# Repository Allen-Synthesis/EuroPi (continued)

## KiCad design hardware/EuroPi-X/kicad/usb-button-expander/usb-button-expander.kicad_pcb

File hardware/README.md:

# Hardware Overview
There are multiple versions of the hardware documented in this directory, the original EuroPi (through-hole), the new EuroPi-SMD (surface-mount), and a stripboard version (stripboard). Each has a different build guide and bill of materials, so make sure you follow the one you want to build.

**[surface-mount](surface-mount/)**: The simplest to DIY as you only need to solder on the components which stick through the panel, i.e. the jacks, knobs etc. All of the other circuitry is soldered onto the PCB already.

**[through-hole](through-hole/)**: A slightly more in depth build as you need to solder on every component, however only through-hole components are used, so this isn't as hard as it sounds. This is the build most people have made and was previously the only publicly available build at all.

**[stripboard](stripboard/)**: A much rougher layout and does not use a PCB at all, but instead uses 'stripboard'. This hasn't been tested nearly as much as the other two, but people have successfully built it and shared their version on Discord. Not developed or maintained by Allen Synthesis.

# Hardware Specifications
All hardware variants share the same specifications as the components and schematics are the same.

## Outputs
- 1k Output Impedance
- RC filter smoothed PWM
- ~1.5kHz Maximum usable frequency (without changing RC values)
- 0-10V

## Analogue Input
- 100k Input Impedance
- 0-12V Readable Range
- Protected for ±12V (TL074 limits, MCP6002 will always clip to ±3.3V)

## Digital Input
- 100k Input Impedance
- 0.8V threshold to read as high

## OLED
- SSD1306 0.91"
- 128 x 32 pixels
- I2C Protocol

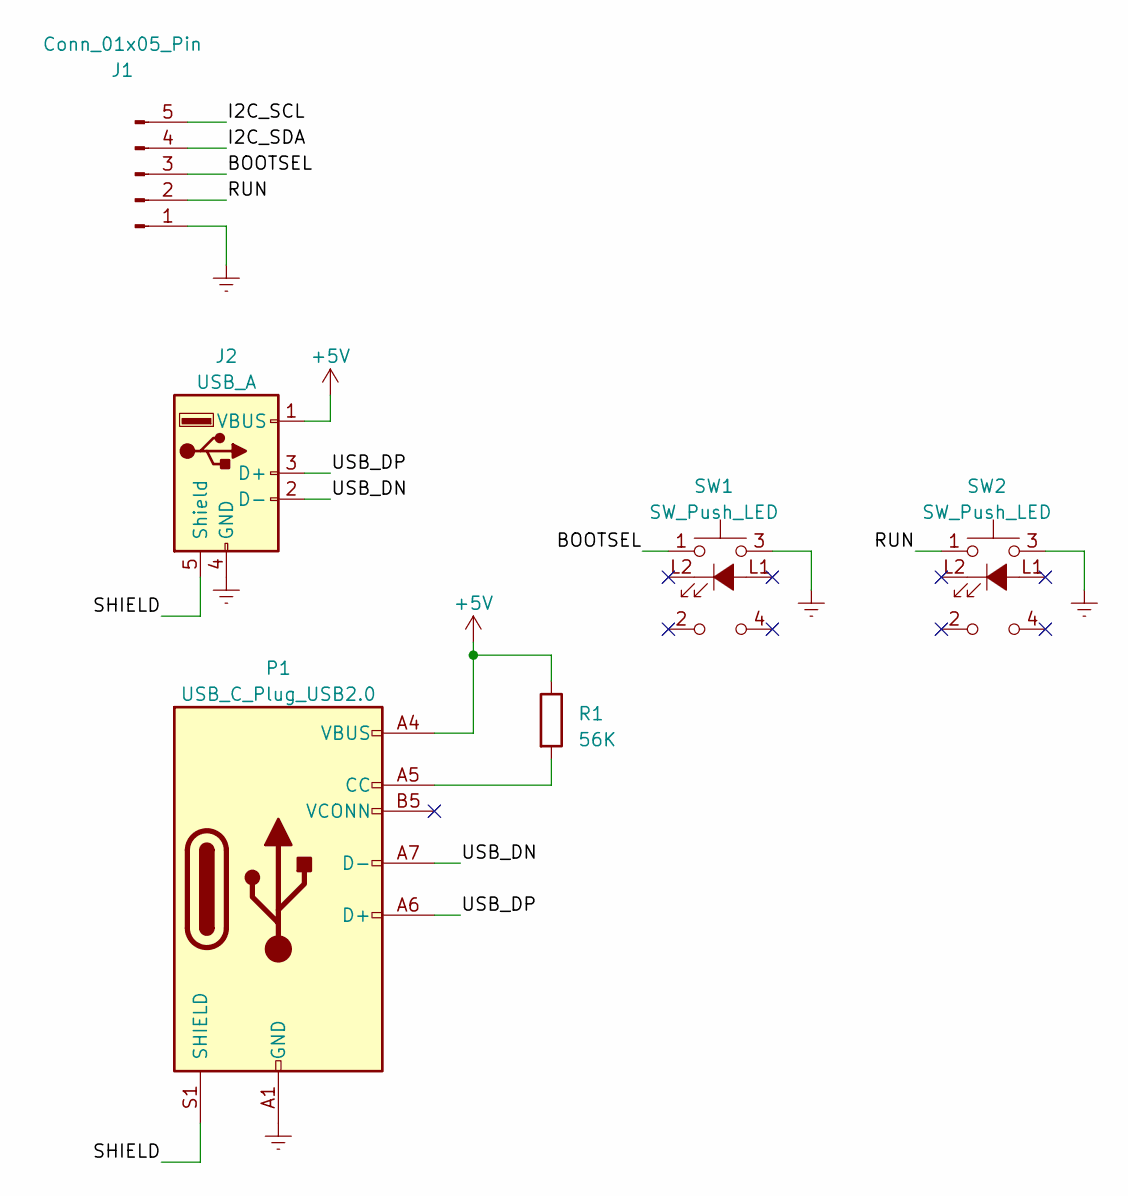
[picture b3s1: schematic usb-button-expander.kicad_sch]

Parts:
J1: Conn_01x05_Pin; PinHeader_1x05_P2.54mm_Vertical
J2: USB_A; CN22155 USB 2.0 Female Connector
P1: USB_C_Plug_USB2.0; USB_C_Receptacle_GCT_USB4115-03-C
R1: 56K; R_0402_1005Metric
SW1, SW2: SW_Push_LED; PB01-109TL low Profile Illuminated Button

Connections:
+5V: J2.1 (VBUS), P1.A4 (VBUS), P1.A9 (VBUS), P1.B4 (VBUS), P1.B9 (VBUS), R1.1
/BOOTSEL: J1.3, SW1.1
/I2C_SCL: J1.5
/I2C_SDA: J1.4
/RUN: J1.2, SW2.1
/SHIELD: J2.5 (Shield), P1.S1 (SHIELD)
/USB_DN: J2.2 (D-), P1.A7 (D-)
/USB_DP: J2.3 (D+), P1.A6 (D+)
Earth: J1.1, J2.4 (GND), P1.A1 (GND), P1.A12 (GND), P1.B1 (GND), P1.B12 (GND), SW1.3, SW2.3
unnamed: P1.A5 (CC), R1.2

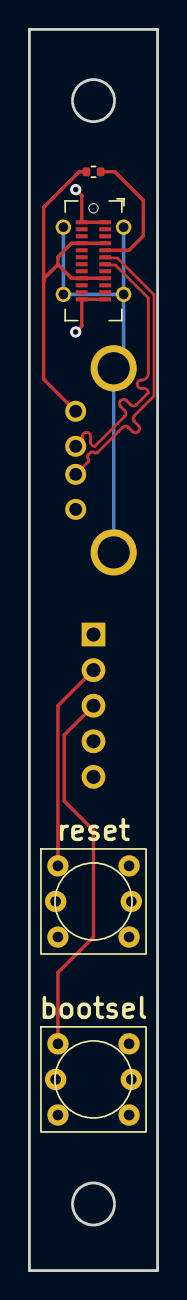
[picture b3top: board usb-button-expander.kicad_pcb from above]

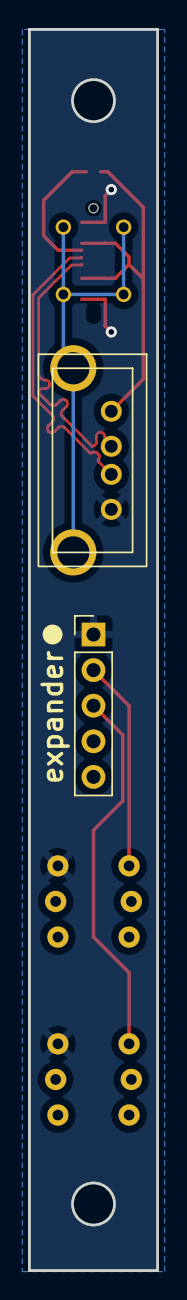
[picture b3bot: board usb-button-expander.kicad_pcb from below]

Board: 2 copper layers, 9.1 x 88.6 mm, 6 parts (2 on the bottom side), 8 nets.

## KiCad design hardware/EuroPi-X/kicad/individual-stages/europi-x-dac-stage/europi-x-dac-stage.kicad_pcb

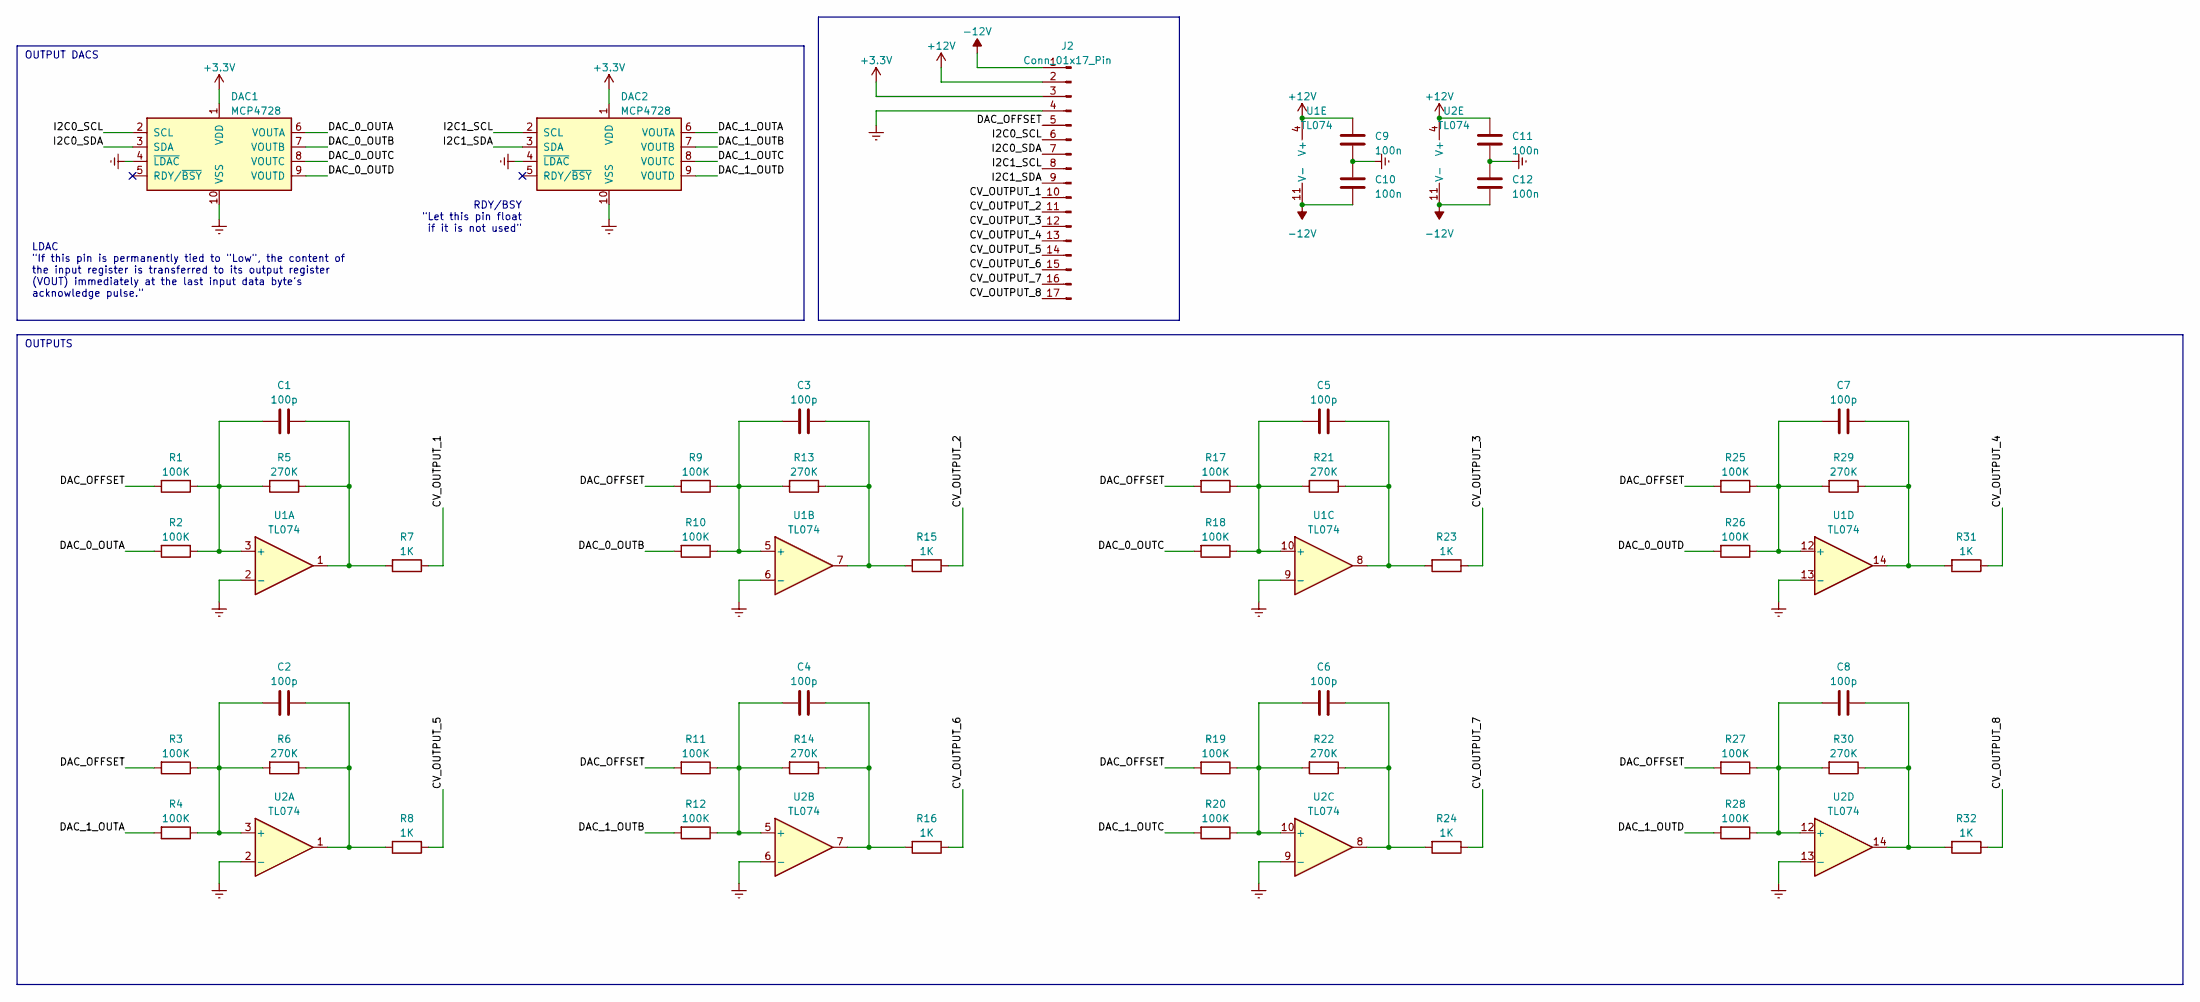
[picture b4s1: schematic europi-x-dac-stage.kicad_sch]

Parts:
C1, C2, C3, C4, C5, C6, C7, C8: 100p; C_0402_1005Metric
C9, C10, C11, C12: 100n; C_0402_1005Metric
DAC1, DAC2: MCP4728; MSOP-10_3x3mm_P0.5mm
J2: Conn_01x17_Pin; PinHeader_1x17_P2.54mm_Vertical
R1, R2, R3, R4, R9, R10, R11, R12, R17, R18, R19, R20, R25, R26, R27, R28: 100K; R_0402_1005Metric
R5, R6, R13, R14, R21, R22, R29, R30: 270K; R_0402_1005Metric
R7, R8, R15, R16, R23, R24, R31, R32: 1K; R_0402_1005Metric
U1, U2: TL074; SOIC-14_3.9x8.7mm_P1.27mm

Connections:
+3.3V: DAC1.1 (VDD), DAC2.1 (VDD), J2.3
+12V: C9.1, C11.1, J2.2, U1.4 (V+), U2.4 (V+)
-12V: C10.2, C12.2, J2.1, U1.11 (V-), U2.11 (V-)
/CV_OUTPUT_1: J2.10, R7.1
/CV_OUTPUT_2: J2.11, R15.1
/CV_OUTPUT_3: J2.12, R23.1
/CV_OUTPUT_4: J2.13, R31.1
/CV_OUTPUT_5: J2.14, R8.1
/CV_OUTPUT_6: J2.15, R16.1
/CV_OUTPUT_7: J2.16, R24.1
/CV_OUTPUT_8: J2.17, R32.1
/DAC_0_OUTA: DAC1.6 (VOUTA), R2.2
/DAC_0_OUTB: DAC1.7 (VOUTB), R10.2
/DAC_0_OUTC: DAC1.8 (VOUTC), R18.2
/DAC_0_OUTD: DAC1.9 (VOUTD), R26.2
/DAC_1_OUTA: DAC2.6 (VOUTA), R4.2
/DAC_1_OUTB: DAC2.7 (VOUTB), R12.2
/DAC_1_OUTC: DAC2.8 (VOUTC), R20.2
/DAC_1_OUTD: DAC2.9 (VOUTD), R28.2
/DAC_OFFSET: J2.5, R1.2, R3.2, R9.2, R11.2, R17.2, R19.2, R25.2, R27.2
/I2C0_SCL: DAC1.2 (SCL), J2.6
/I2C0_SDA: DAC1.3 (SDA), J2.7
/I2C1_SCL: DAC2.2 (SCL), J2.8
/I2C1_SDA: DAC2.3 (SDA), J2.9
Earth: C9.2, C10.1, C11.2, C12.1, DAC1.4 (~LDAC), DAC1.10 (VSS), DAC2.4 (~LDAC), DAC2.10 (VSS), J2.4, U1.2 (-), U1.6 (-), U1.9 (-), U1.13 (-), U2.2 (-), U2.6 (-), U2.9 (-), U2.13 (-)
unnamed: C1.2, R5.1, R7.2, U1.1
unnamed: C2.2, R6.1, R8.2, U2.1
unnamed: C3.2, R13.1, R15.2, U1.7
unnamed: C4.2, R14.1, R16.2, U2.7
unnamed: C5.2, R21.1, R23.2, U1.8
unnamed: C6.2, R22.1, R24.2, U2.8
unnamed: C7.2, R29.1, R31.2, U1.14
unnamed: C8.2, R30.1, R32.2, U2.14
unnamed: C1.1, R1.1, R2.1, R5.2, U1.3 (+)
unnamed: C3.1, R9.1, R10.1, R13.2, U1.5 (+)
unnamed: C5.1, R17.1, R18.1, R21.2, U1.10 (+)
unnamed: C7.1, R25.1, R26.1, R29.2, U1.12 (+)
unnamed: C2.1, R3.1, R4.1, R6.2, U2.3 (+)
unnamed: C4.1, R11.1, R12.1, R14.2, U2.5 (+)
unnamed: C6.1, R19.1, R20.1, R22.2, U2.10 (+)
unnamed: C8.1, R27.1, R28.1, R30.2, U2.12 (+)

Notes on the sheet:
LDAC "If this pin is permanently tied to "Low", the content of the input register is transferred to its output register (VOUT) immediately at the last input data byte's acknowledge pulse."
RDY/BSY "Let this pin float if it is not used"
OUTPUTS
OUTPUT DACS

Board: 2 copper layers, 49 parts (0 on the bottom side), 41 nets, no tracks yet.

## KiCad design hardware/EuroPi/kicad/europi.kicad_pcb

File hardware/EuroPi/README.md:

# Hardware Specifications

## Outputs
- 1k Output Impedance
- RC filter smoothed PWM
- ~1.5kHz Maximum usable frequency (without changing RC values)
- 0.000176V Maximum ripple peak-to-peak
- 0.0108s Settle time from 0% to 90% duty cycle
- 0-10V

## Analogue Input
- 100k Input Impedance
- 0-12V Readable Range
- Protected for ±36V (TL074 limits, MCP6002 will always clip to ±3.3V)

## Digital Input
- 100k Input Impedance
- 0.8V threshold to read as high

## OLED
- SSD1306 0.91"
- 128 x 32 pixels
- I2C Protocol

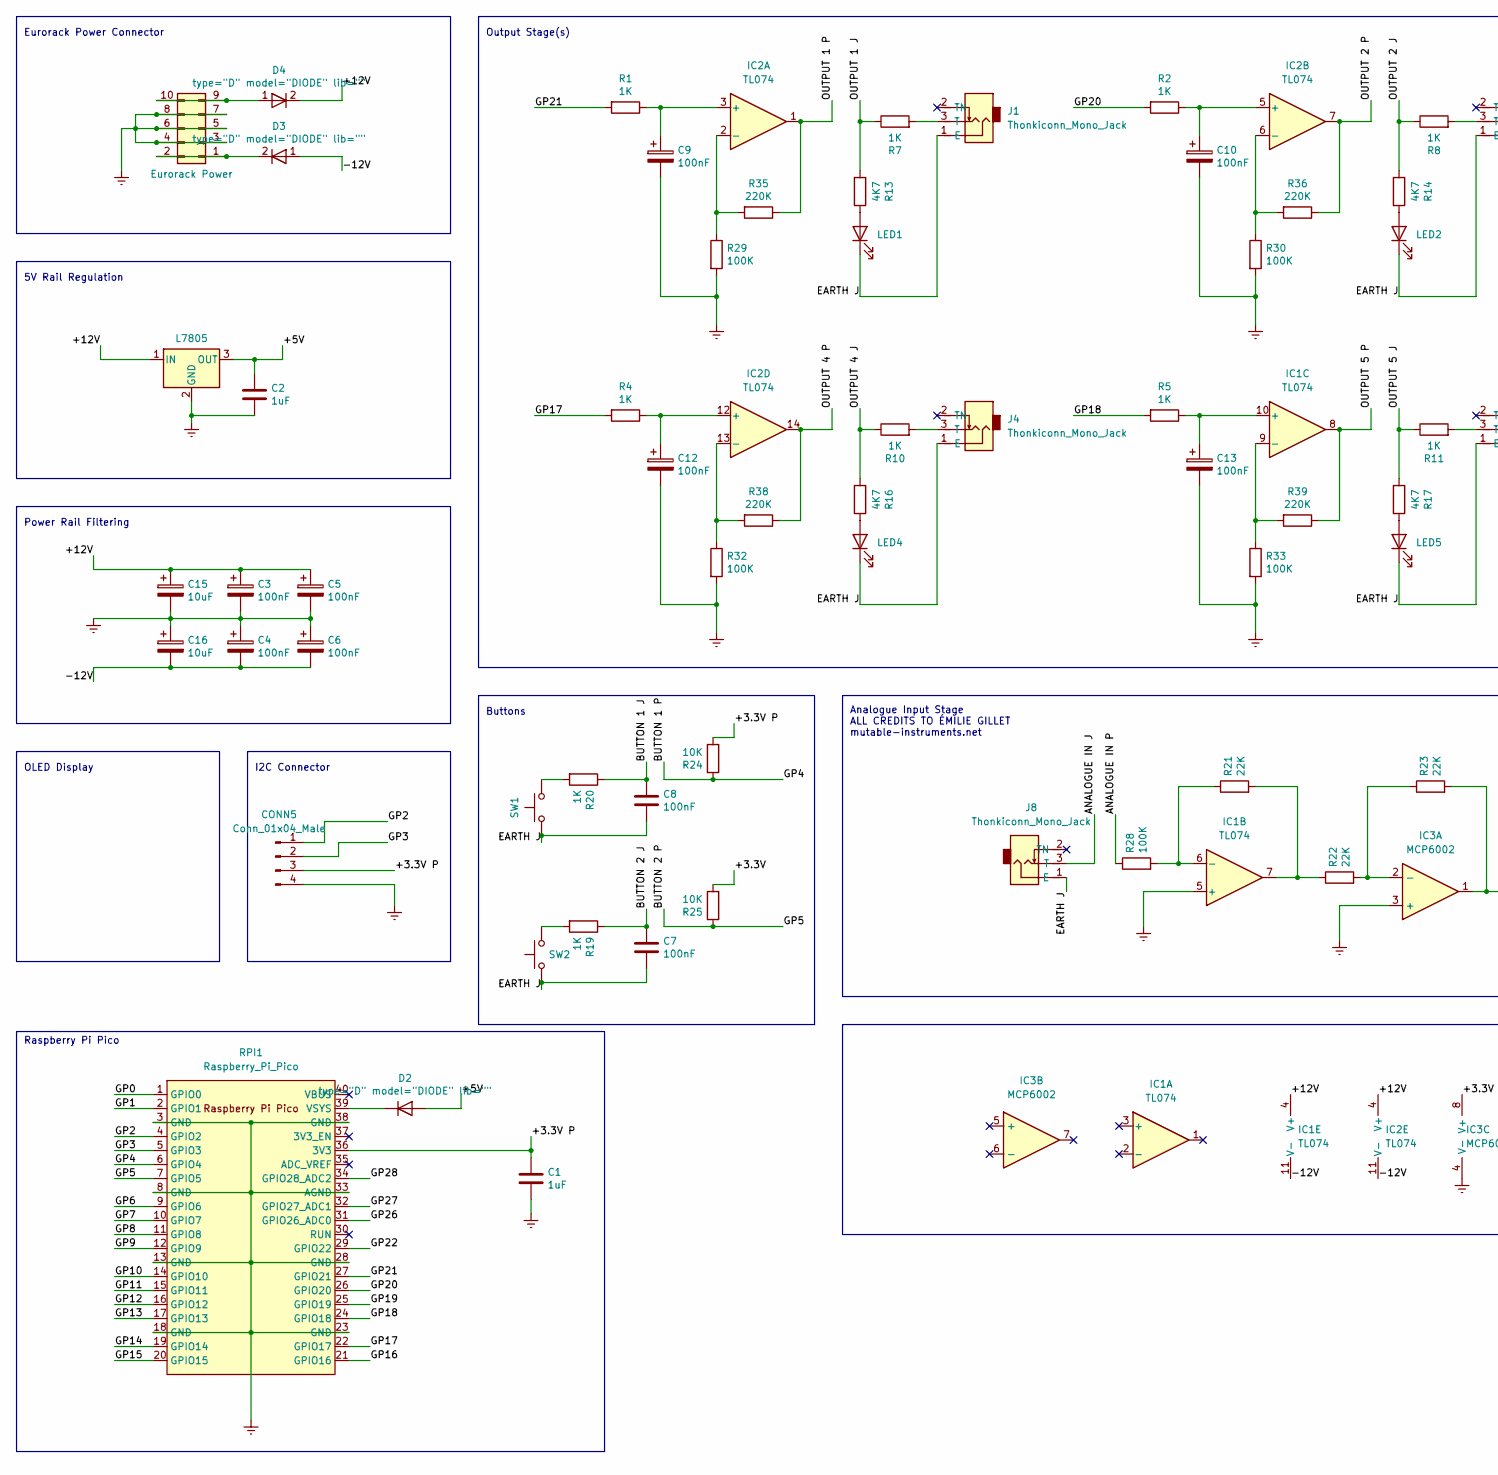
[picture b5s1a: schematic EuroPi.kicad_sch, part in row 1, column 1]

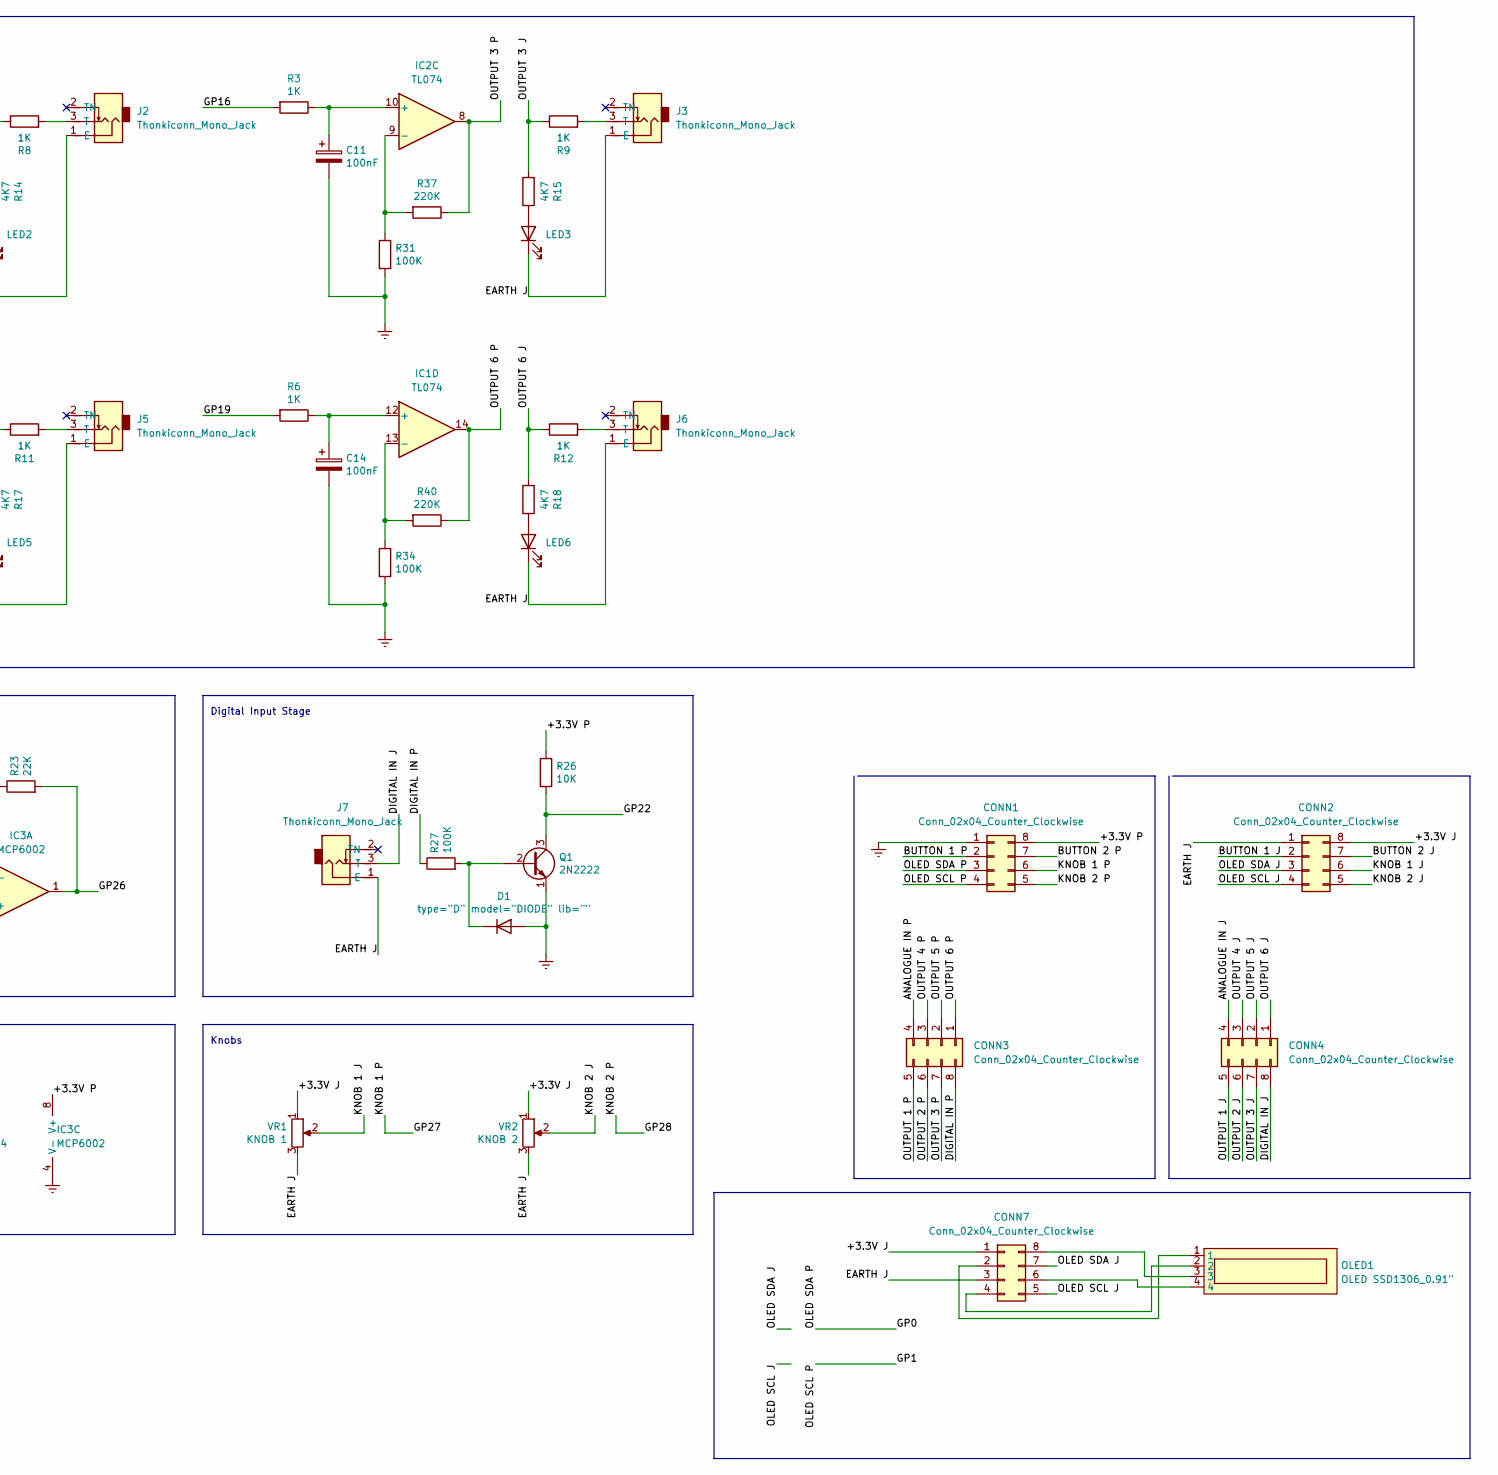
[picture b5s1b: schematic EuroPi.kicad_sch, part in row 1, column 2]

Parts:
C1, C2: 1uF; CP_Radial_D5.0mm_P2.50mm
C3, C4, C5, C6, C7, C8, C9, C10, C11, C12, C13, C14: 100nF; Capacitor Small Non-Polarised
C15, C16: 10uF; CP_Radial_D8.0mm_P3.80mm
CONN1, CONN2, CONN3, CONN4, CONN7: Conn_02x04_Counter_Clockwise; PinHeader_2x04_P2.54mm_Vertical
CONN5: Conn_01x04_Male; PinHeader_1x04_P2.54mm_Vertical
D1, D2, D3, D4: type="D" model="DIODE" lib=""; Schottky Diode
EuroPower1: Eurorack Power; Eurorack Power Header Unlabeled
IC1, IC2: TL074; DIP-14 IC Socket
IC3: MCP6002; DIP-8 IC Socket
J1, J2, J3, J4, J5, J6, J7, J8: Thonkiconn_Mono_Jack; Thonkiconn Mono Jack
LED1, LED2, LED3, LED4, LED5, LED6: LED; LED 3mm
OLED1: OLED SSD1306_0.91"; OLED SSD1306 0.91
Q1: 2N2222; TO-92
R1, R2, R3, R4, R5, R6, R7, R8, R9, R10, R11, R12, R19, R20: 1K; Resistor 0.25W Through-Hole
R13, R14, R15, R16, R17, R18: 4K7; Resistor 0.25W Through-Hole
R21, R22, R23: 22K; Resistor 0.25W Through-Hole
R24, R25, R26: 10K; Resistor 0.25W Through-Hole
R27, R28, R29, R30, R31, R32, R33, R34: 100K; Resistor 0.25W Through-Hole
R35, R36, R37, R38, R39, R40: 220K; Resistor 0.25W Through-Hole
REG1: L7805; TO-220-3_Vertical
RPI1: Raspberry_Pi_Pico; Raspberry Pi Pico
SW1, SW2: SW_Push; Switch Tactile Momentary C&K
VR1: KNOB 1; Potentiometer 9mm Vertical Linear Centred
VR2: KNOB 2; Potentiometer 9mm Vertical Linear Centred

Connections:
/+3.3V: R25.2
/+3.3V J: CONN2.8, CONN7.1, VR1.1, VR2.1
/+3.3V P: C1.1, CONN1.8, CONN5.3, IC3.8 (V+), R24.2, R26.1, RPI1.36 (3V3)
/+5V: C2.1, D2.1 (A), REG1.3 (OUT)
/+12V: C3.1, C5.1, C15.1, D4.2 (K), IC1.4 (V+), IC2.4 (V+), REG1.1 (IN)
/-12V: C4.2, C6.2, C16.2, D3.1 (A), IC1.11 (V-), IC2.11 (V-)
/ANALOGUE IN J: CONN4.4, J8.3 (T)
/ANALOGUE IN P: CONN3.4, R28.1
/BUTTON 1 J: C8.1, CONN2.2, R20.1
/BUTTON 1 P: CONN1.2, R24.1, RPI1.6 (GPIO4)
/BUTTON 2 J: C7.1, CONN2.7, R19.1
/BUTTON 2 P: CONN1.7, R25.1, RPI1.7 (GPIO5)
/DIGITAL IN J: CONN4.8, J7.3 (T)
/DIGITAL IN P: CONN3.8, R27.1
/EARTH J: C7.2, C8.2, CONN2.1, CONN7.3, J1.1 (E), J2.1 (E), J3.1 (E), J4.1 (E), J5.1 (E), J6.1 (E), J7.1 (E), J8.1 (E), LED1.1 (K), LED2.1 (K), LED3.1 (K), LED4.1 (K), LED5.1 (K), LED6.1 (K), SW1.1, SW2.1, VR1.3, VR2.3
/GP0: CONN1.3, RPI1.1 (GPIO0)
/GP1: CONN1.4, RPI1.2 (GPIO1)
/GP2: CONN5.1, RPI1.4 (GPIO2)
/GP3: CONN5.2, RPI1.5 (GPIO3)
/GP6: RPI1.9 (GPIO6)
/GP7: RPI1.10 (GPIO7)
/GP8: RPI1.11 (GPIO8)
/GP9: RPI1.12 (GPIO9)
/GP10: RPI1.14 (GPIO10)
/GP11: RPI1.15 (GPIO11)
/GP12: RPI1.16 (GPIO12)
/GP13: RPI1.17 (GPIO13)
/GP14: RPI1.19 (GPIO14)
/GP15: RPI1.20 (GPIO15)
/GP16: R3.2, RPI1.21 (GPIO16)
/GP17: R4.2, RPI1.22 (GPIO17)
/GP18: R5.2, RPI1.24 (GPIO18)
/GP19: R6.2, RPI1.25 (GPIO19)
/GP20: R2.2, RPI1.26 (GPIO20)
/GP21: R1.2, RPI1.27 (GPIO21)
/GP22: Q1.3 (C), R26.2, RPI1.29 (GPIO22)
/GP26: IC3.1, R23.2, RPI1.31 (GPIO26_ADC0)
/GP27: CONN1.6, RPI1.32 (GPIO27_ADC1)
/GP28: CONN1.5, RPI1.34 (GPIO28_ADC2)
/KNOB 1 J: CONN2.6, VR1.2
/KNOB 2 J: CONN2.5, VR2.2
/OLED SCL J: CONN2.4, CONN7.5
/OLED SDA J: CONN2.3, CONN7.7
/OUTPUT 1 J: CONN4.5, R7.1, R13.2
/OUTPUT 1 P: CONN3.5, IC2.1, R35.1
/OUTPUT 2 J: CONN4.6, R8.1, R14.2
/OUTPUT 2 P: CONN3.6, IC2.7, R36.1
/OUTPUT 3 J: CONN4.7, R9.1, R15.2
/OUTPUT 3 P: CONN3.7, IC2.8, R37.1
/OUTPUT 4 J: CONN4.3, R10.1, R16.2
/OUTPUT 4 P: CONN3.3, IC2.14, R38.1
/OUTPUT 5 J: CONN4.2, R11.1, R17.2
/OUTPUT 5 P: CONN3.2, IC1.8, R39.1
/OUTPUT 6 J: CONN4.1, R12.1, R18.2
/OUTPUT 6 P: CONN3.1, IC1.14, R40.1
Earth: C1.2, C2.2, C3.2, C4.1, C5.2, C6.1, C9.2, C10.2, C11.2, C12.2, C13.2, C14.2, C15.2, C16.1, CONN1.1, CONN5.4, D1.1 (A), EuroPower1.3, EuroPower1.4, EuroPower1.5, EuroPower1.6, EuroPower1.7, EuroPower1.8, IC1.5 (+), IC3.3 (+), IC3.4 (V-), Q1.1 (E), R29.2, R30.2, R31.2, R32.2, R33.2, R34.2, REG1.2 (GND), RPI1.3 (GND), RPI1.8 (GND), RPI1.13 (GND), RPI1.18 (GND), RPI1.23 (GND), RPI1.28 (GND), RPI1.33 (AGND), RPI1.38 (GND)
unnamed: CONN7.2, OLED1.1
unnamed: CONN7.4, OLED1.2
unnamed: CONN7.6, OLED1.4
unnamed: CONN7.8, OLED1.3
unnamed: D1.2 (K), Q1.2 (B), R27.2
unnamed: D2.2 (K), RPI1.39 (VSYS)
unnamed: D3.2 (K), EuroPower1.1, EuroPower1.2
unnamed: D4.1 (A), EuroPower1.9, EuroPower1.10
unnamed: IC1.7, R21.2, R22.1
unnamed: IC1.6 (-), R21.1, R28.2
unnamed: C13.1, IC1.10 (+), R5.1
unnamed: IC1.9 (-), R33.1, R39.2
unnamed: C14.1, IC1.12 (+), R6.1
unnamed: IC1.13 (-), R34.1, R40.2
unnamed: C9.1, IC2.3 (+), R1.1
unnamed: IC2.2 (-), R29.1, R35.2
unnamed: C10.1, IC2.5 (+), R2.1
unnamed: IC2.6 (-), R30.1, R36.2
unnamed: C11.1, IC2.10 (+), R3.1
unnamed: IC2.9 (-), R31.1, R37.2
unnamed: C12.1, IC2.12 (+), R4.1
unnamed: IC2.13 (-), R32.1, R38.2
unnamed: IC3.2 (-), R22.2, R23.1
unnamed: J1.3 (T), R7.2
unnamed: J2.3 (T), R8.2
unnamed: J3.3 (T), R9.2
unnamed: J4.3 (T), R10.2
unnamed: J5.3 (T), R11.2
unnamed: J6.3 (T), R12.2
unnamed: LED1.2 (A), R13.1
unnamed: LED2.2 (A), R14.1
unnamed: LED3.2 (A), R15.1
unnamed: LED4.2 (A), R16.1
unnamed: LED5.2 (A), R17.1
unnamed: LED6.2 (A), R18.1
unnamed: R19.2, SW2.2
unnamed: R20.2, SW1.2

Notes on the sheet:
OLED Display
Buttons
5V Rail Regulation
Analogue Input Stage ALL CREDITS TO ÉMILIE GILLET mutable-instruments.net
Power Rail Filtering
Eurorack Power Connector
I2C Connector
Digital Input Stage
Raspberry Pi Pico
Output Stage(s)
Knobs

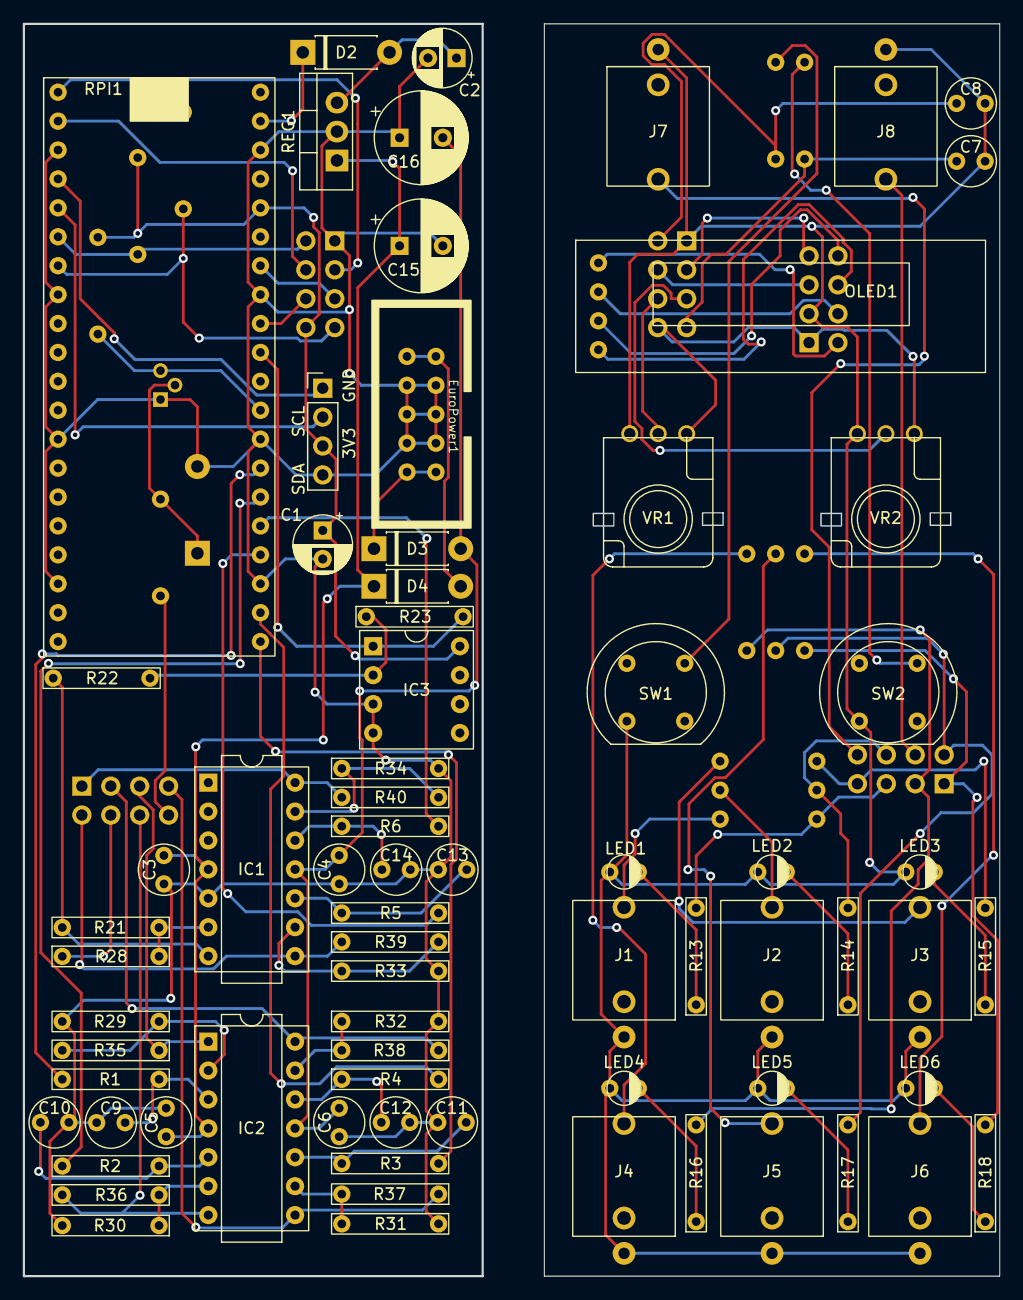
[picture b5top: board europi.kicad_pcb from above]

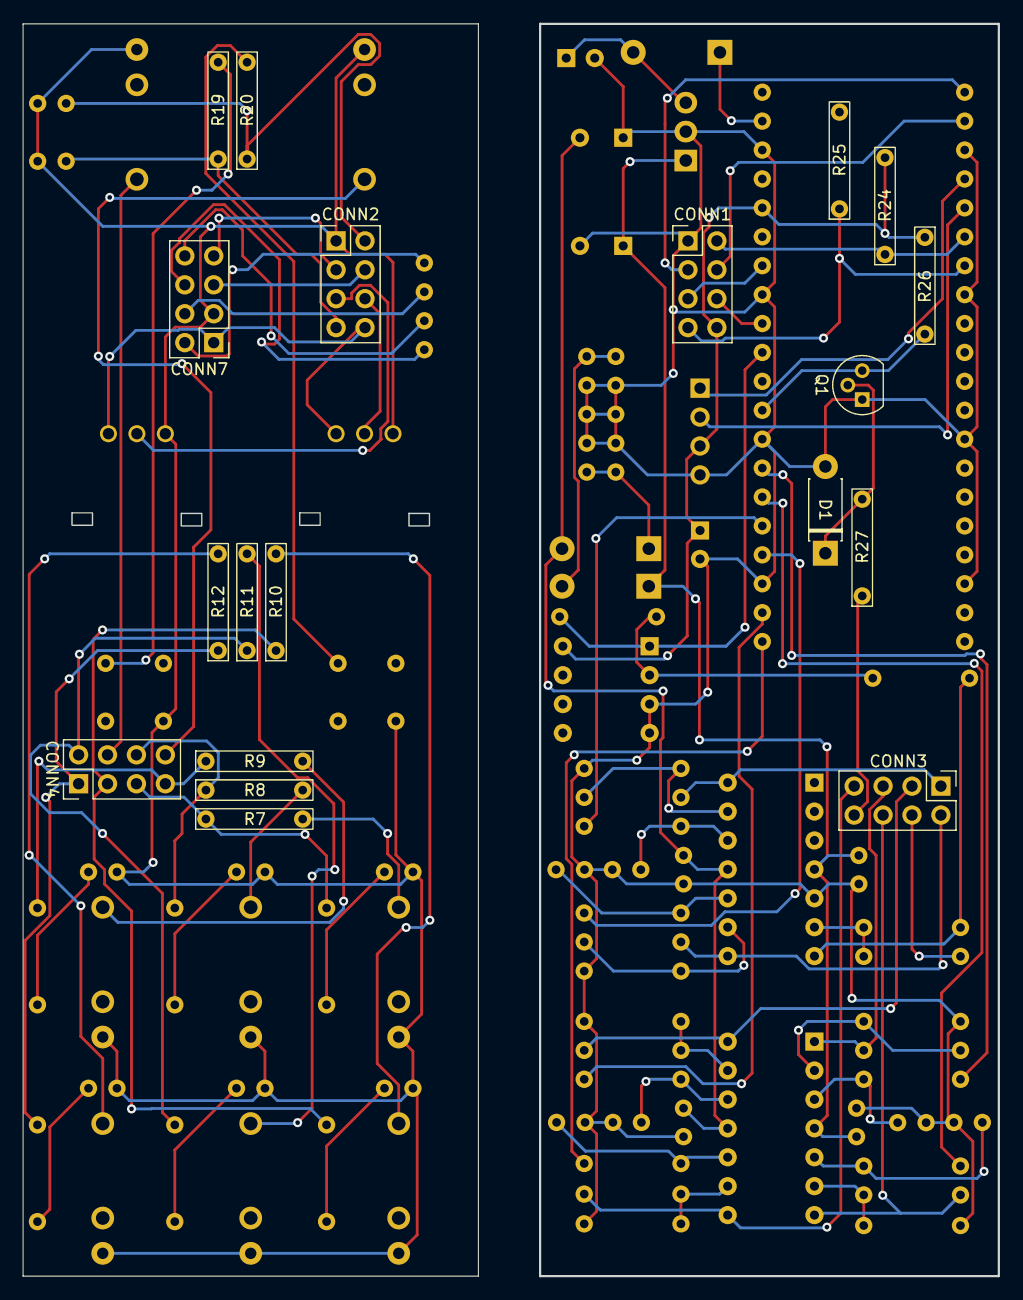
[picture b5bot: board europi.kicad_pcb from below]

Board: 2 copper layers, 85.7 x 110.0 mm, 92 parts (19 on the bottom side), 82 nets.

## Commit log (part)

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2025-03-07 Add a dedicated text logging class so we can have consistent text output across the firmware
2025-03-07 Add newline to end of file
2025-03-07 Formatting
2025-03-07 Increase connection timeout to 15s
2025-03-07 Add http_control.md, add HttpControl to readme & main menu
2025-03-07 Start adding support for Open Sound Control over UDP
2025-03-07 Fix float encoding, various debugging fixes
2025-03-07 Disable sending the knob/button/input jack status for now
2025-03-07 Fix fmt on/off
2025-03-07 Ignore formatting of disabled code
2025-03-07 Whitespace around operator
2025-03-07 Re-enable sending data back to TouchOSC, increase send rate to 20Hz. Show a 'waiting...' screen with the local IP address until the first packet is received
2025-03-07 Show a loading message when wifi is connecting, force-show the oled when resetting state
2025-03-07 Fix a typo when sending floats
2025-03-07 Add options for static IP connect. Reduce timeout back to 15 seconds, but add 3 tries (max)
2025-03-07 Add a log entry about last_crash for completeness
2025-03-07 Add display-only support for strings to the configuration editor
2025-03-07 Space before type hint
2025-03-07 Reduce the size of the connecting text so it fits on screen
2025-03-07 Remove note about terminal not working; seems to be a browser bug on my end. Add Thonny configuration notes
2025-03-07 Add desktop interface program for converting 8mu's MIDI messages to OSC for EuroPi
2025-03-07 Change mock_hardware to import from europi_hardware
2025-03-07 bytes -> bits in comment
2025-03-08 Spacing between type hints
2025-03-08 Make sure WebREPL is in the WiFi section of the config editor
2025-03-08 Add documentation for all wifi defaults
2025-03-08 Add notes about security to the configuration doc
2025-03-08 Line wrapping
2025-03-08 Fix the default i2c timeout in the config documentation
2025-03-09 Fix OSC packet parsing to be compatible with OSC Controller. Strip trailing / from address if present, fix string parsing to prevent an overflow
2025-03-10 Remove TODO items from mock network module, add additional constants & functions
2025-03-11 Add a new section about desktop scripts
2025-03-11 Simplify the UI rendering logic further
2025-03-15 Don't log malformed packets. Leave the code available for debugging, but there's no need to use this much disk capacity
2025-03-16 Rename HTTP Interface in readme
2025-03-16 Wireless, Networking Support for Pico W, Pico 2 W (#416)
    * Add StringConfigPoint
    * Add wifi connection implementation
    * Add wifi, NTP configurations to `experimental_config`
    * Add NTP implementation for realtime clock support
    * Add additional module dependencies needed for NTP
    * Catch import errors in the wifi and ntp modules as appropriate, re-raising them with our wrapper errors
2025-03-17 Remove `{meth}` tag
    Method has been moved, causing this tag to fail CI
2025-03-17 Fix import path to resolve failing documentation CI
2025-03-17 Add additional modules to the generated api docs
2025-03-17 Run the doc generation on this branch to verify CI actually works properly
2025-03-17 Remove custom_font from autodocs
2025-03-17 Remove JSON examples from docstrings, add reference to main documentation
2025-03-17 Remove unnecessary import, fix clock source docstrings
2025-03-17 Remvove indentation, fix newlines
2025-03-17 Change to sphinx-style code blocks
2025-03-17 Add line break between parameters and return
2025-03-17 Remove indendented sub-list
2025-03-17 Reformat long parameter descriptions
2025-03-17 deploy: 6c24a9919187af16a15d5efdb8290e94ed77150a
2025-03-17 Add newlines around new try/catch
2025-03-17 Fix failing autodoc CI (#424)
    * Fix docstrings, autodoc configurations
2025-03-17 Replace javadoc-style docstrings with sphinx-style ones
2025-03-17 Use Sphinx-style docstrings (#425)
    * Replace javadoc-style docstrings with sphinx-style ones
2025-03-17 Remove explicit code-block
2025-03-17 Use sphinx-style lists, add required newlines between items
2025-03-17 Add line-wrapping
2025-03-17 Fix Sphinx errors in updated docstrings (#426)
2025-03-17 Add __init__ files with docstrings for namespaces, move constructor parameters into the class docstrings
2025-03-17 Remove mentions of specific Micropython versions; these go out-of-date too fast to keep up with them
2025-03-17 Newlines
2025-03-18 Add missing docstrings, parameters to firmware modules
    * Move constructor parameters to class docstring
    * Add __init__ files with docstrings for namespaces, move constructor parameters into the class docstrings
    * Remove mentions of specific Micropython versions; these go out-of-date too fast to keep up with them
    * Add a docstring to version.py
2025-03-18 deploy: e8fc58d64804bd358a3b69a17ca20de4abba6b05
2025-03-18 deploy: dae17d40e0aaedb6b7f9bb7ece6d9a0e7f7a0150
2025-03-18 deploy: 77d8caa62e884aa5b697a5206ae5240ece997501
2025-03-25 Add additional steps to build UF2 files for all available boards. Note: Pico 2 W is _not_ available yet, so hold off merging this until it is
2025-03-26 Build UF2 files for additional boards (#429)
    * Add additional steps to build UF2 files for all available boards. Note: Pico 2 W is _not_ available yet, but will be added in a future update
2025-03-26 Update CI to build & store all boards
2025-04-12 Add initial version of bouncing pixels
2025-04-12 Add documentation for bouncing pixels
2025-04-12 Remove unused and commented out code
2025-04-12 Swap places for consistency
2025-04-15 Add local development import paths for linter assistance
2025-04-15 Render on timer callback
2025-04-15 Remove unused import
2025-04-15 Add some comments; clean up
2025-04-15 Replace aspect ratio with width
2025-04-15 Update script docs
2025-04-16 Uncap poll frequency; change default to 30
2025-04-16 Bump the Micropython version for UF2 builds to 1.25.0, enable Pico 2 W builds
2025-05-07 Catch keyboard interrupts in Lutra so the background thread terminates cleanly when debugging
2025-05-07 Add config parameters to change all of the input & output topics (#430)
2025-05-07 Limit drawing to max of 30FPS
2025-05-08 Use basic math to check the knob change instead of doing string conversions
2025-05-09 Don't check the USB connection for secondary threads; just catch the keyboard interrupts (which also fire when the USB terminal connects)
2025-05-13 Refactor Conway to use both cores
2025-05-20 Exit both threads on keyboard interrupt
2025-05-20 Implement lock for shared data
2025-05-20 Update digital input helper inside of poll function
2025-05-20 Revert to width on first knob bank layer
2025-05-20 Remove debugging code
2025-05-31 Catch keyboard interrupts in multi-threaded programs (#434)
    * Catch keyboard interrupts in Lutra so the background thread terminates cleanly when debugging
    * Update threading examples to include catching the keyboard interrupt to make debugging easier
    * Don't check is_running & the USB status in the foreground thread
    * Don't check the USB connection for secondary threads; just catch the keyboard interrupts (which also fire when the USB terminal connects)
2025-05-31 Update CI to build & store all boards (#431)
    * Bump the Micropython version for UF2 builds to 1.25.0, enable Pico 2 W builds
2025-05-31 Update files for final release step
2025-05-31 Use integer math in init; we've removed all other isntances of bit-shifting instead of multiplying
2025-05-31 Fix some typos in readmes
2025-06-01 Fix line lengths in bezier readme
2025-06-01 Remove author and tags from bouncing_pixels readme
2025-06-01 Re-organize coin_toss readme, remove debugging section as it's not needed anymore
2025-06-01 Update formatting for Conway's readme, add a note about voltage limits
2025-06-01 Fix while loop condition formatting
2025-06-01 Best result -> Best results
2025-06-01 Fix formatting of dcsn2 readme
2025-06-01 Fix formatting of envelope generator readme
2025-06-01 Fix formatting of euclid readme
2025-06-01 Fix formatting of G&T readme
2025-06-01 Fix formatting of harmonic_lfos readme
2025-06-01 Fix formatting of Kompari readme, add a link to the Kompari product page. Explain the mathematics a little more clearly
2025-06-01 Fix formatting for Lutra readme, add dedicated I/O section
2025-06-01 Fix formatting of menu readme
2025-06-01 Fix line wrapping in Ocean Surge
2025-06-01 Add links to ALM's product pages
2025-06-01 Fix formatting of Pet Rock readme
2025-06-01 Fix formatting of poly square readme. Move controls to be the first section after the intro to stay consistent with everything else
2025-06-01 Fix formatting of radio scanner readme
2025-06-01 Fix formatting of slopes readme
2025-06-01 Fix formatting of turning machine readme
2025-06-01 Remove programs that require wifi from the main menu if EuroPi doesn't have a wifi-enabled Pico; these programs will not work
2025-06-06 Fix typos, formatting for contrib readmes (#437)
2025-06-06 deploy: d9bf0b16b7c41cc5eb718a99f3b5b425f82a6ede
2025-06-06 Remove programs that require wifi from the main menu if EuroPi doesn't have a wifi-enabled Pico; these programs will not work (#439)
2025-06-10 fix: OSC: add missing self in `set_cvs()` for `/europi/cvs`
    Due to missing self in `set_cvs()` the OSC address `/europi/cvs` fails.
    I made the fix in my EuroPi and now it works!
2025-07-01 Copy the `tools` directory when building the UF2 via CI
2025-07-02 Update programming_instructions.md (#441)
    Fix the description of `europi-contrib`'s `main.py` in the programming instructions.
    Resolves https://github.com/Allen-Synthesis/EuroPi/issues/440
2025-07-31 Re-add extra newline before the class (linting)
2025-09-08 Add `discrete`, `continuous` modes to Binary Counter (#445)
    * Change binary counter to have discrete or continuous modes.
    * Limit min k to 1 instead of 0.
    * Add a screensaver to Binary Counter
2025-10-29 conway - performance improvements
    Refactor Conway class for performance improvements.
    Optimize memory usage with 1D arrays and micropython native/ iper functions.
2025-11-04 Aligning menu to Europi menu format
2025-11-25 Linting
2025-11-28 Add external clock mode to the readme
2025-11-28 Add a section about configuring VS Code to the programming instructions
2025-11-28 deploy: a0adbeac25f4543bbabb6ed9451d87ec98711ab5
2025-12-02 reorganise hardware
2025-12-06 added osc bundle support
2025-12-07 Add preliminary support for single-layer OSC bundles. Recursive bundles are not (yet) supported
2025-12-07 Modify the 8mu desktop script to write bundles at a fixed rate instead of on-the-fly messages. Fix bugs on the Pico when parsing bundles
2025-12-07 Use int.from_bytes rather than doing bitwise operations to parse ints. This might be marginally slower, but it makes the code easier to read
2025-12-07 Remove extra space
2025-12-07 better recursive function + batch messages processing
2025-12-07 Use native code generation to speed up Conway
2025-12-07 deploy: 8cbf912a0f7dba07f539f0abfacd7472c2081786
2026-01-14 add i2c header note
2026-01-14 add version 1.1 number
2026-01-23 correct rev number
2026-01-26 rewrite for clarity
    Updated descriptions for hardware versions to include links and improve clarity.
2026-01-26 remove outdated note
2026-01-27 move skiff instructions to th dir
2026-02-04 reword and correct links
2026-02-04 correct shield links
2026-02-07 minor edits
2026-02-07 Reorganise Hardware (#451)
    * reorganise hardware
    * remove older containing directories
    * add i2c header note
    * fix first revision issues
    * add version 1.1 number
    * update hole sizes
2026-03-09 add resistors to input detect and add oshwa cert mark
2026-03-10 remove extra files and rename others to be consistent with surface-mount
2026-03-10 rename stripboard files for consistency
2026-03-23 fix (#462)
2026-03-30 Minor surface-mount PCB changes (REV 3) (#458)
    * add resistors to input detect and add oshwa cert mark
    * add lcsc part number to d3
2026-04-13 remove www from url
2026-04-23 add i2s port
2026-05-28 align items in Affinity panel
2026-06-28 Add Set Timer, a simple stopwatch with split time and CV control
2026-06-28 Add executable suffix to OffsetVoltages (#469)
2026-06-28 Add external clock mode to Pam's (#450)
    * Re-implement the dynamic BPM version of Pam's for the new menu system
    * Add external clock mode to the readme
    * Don't suppress the screensaver when in external-clock mode
    * Add a section about configuring VS Code to the programming instructions
    * Increase the max clock speed to 300. Add a section about external clocking limitations to the documentation
2026-06-28 Fix quotation marks
